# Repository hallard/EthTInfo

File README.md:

# Ethernet Teleinfo Shield for Olimex ESP32 POE

This shield is to be combined with [Olimex ESP32 POE board](https://www.olimex.com/Products/IoT/ESP32/ESP32-POE/open-source-hardware) to get French energy meter called Teleinfo (AKA TIC) 

It is mainly needed when your smartmeter his far from house and WiFi signal too weak and/or if you don't have power near your smartmeter to power Denky, WeMos Teleinfo or any other type of board. Having Ethernet near smart mater and you done with POE, Olimex board and this Shield.

It has the following features:

- Teleinfo Reader interface
- Blue LED to see if Teleinfo signal is received
- Trimmer to allow TIC sensitivity change without soldering resistors
- RGB User Led

It is a plug and play board, nothing to solder or assemble.

# History

**v1.1**

- Route RGB Led to GPIO5 instead of GPO2 (used by SD card)
- Change RGB Led to 2020 package

**v1.0**

- First fully working prototype

# Detailed Description

## Connectivity

The shield is connected thru Olimex UExt connector

Look at the schematics for more informations, easy to understand. Wiring is as follow:

| Pin Function | ESP32 | 
|  :---        | :---: | 
| Téléinfo Rx  | GPIO36 | 
| RGB Led      | GPIO5 (V1.1) | 
| RGB Led      | GPIO2 (V1.0) | 

Unfortunately RGB led share the same pin than SD Card GPIO2 so if you want to use RGB LED you need to disable SD Card GPIO mapping and vice versa

# Schematics

# Boards

# Firmware 

It's compatible with Arduino IDE, Visual Studio Code and also Micro Python.

You can write your own and use with [LibTeleinfo](https://github.com/hallard/LibTeleinfo) library I wrote if you want to get rid of driving teleinfo stuff (chekout some [examples](ttps://github.com/hallard/LibTeleinfo/tree/master/examples)).

## Tasmota

But I strongly suggest using amazing [Tasmota](https://tasmota.github.io/docs/) firmware, all is already done and well done.

Please check Teleinfo official tasmota [documentation](https://tasmota.github.io/docs/Teleinfo/) so see how to configure your device depending on smartmeter type and what options you need.

### Nicolas's builds

Nicolas @NicolasBernaerts has made awesome changes on Tasmota to be able to show graph of consumption, history and other great features such has:

- Ecowatt server to publish RTE Ecowatt signals
- TCP server to live stream teleinfo data
- FTP server to easily retrieve graph data

You can find more information on his dedicated [repo](https://github.com/NicolasBernaerts/tasmota/tree/master/teleinfo) and also ready made build.

### Tasmota Unofficial builds

Teleinfo is not member of official Tasmota builds. So you need to build your own with `USE_TELEINFO` define. 
But Tasmota team agreed it's not simple to build for end users, and they now provide unofficial build that follow developement branch, this mean you always have an up to date build with latest code available. Of course we added Teleinfo (ESP8266 and ESP32) builds in this unofficial build process so you have nothing to install and compile/link (building). You can't go easier.

And as a cherry on the cake, easy flasher tools (web version and executable one) will present Teleinfo firmware so you are able to flash teleinfo firmware in less than 1 minute. You can check detail [here](https://github.com/Jason2866/Tasmota-specials) but here how to do that.

- Launch [Web Flasher here](https://jason2866.github.io/Tasmota-specials/) 
- Select Teleinfo 
- Select Serial port, and click `install`

Once done something like that

After flashed, you should now see a new access point named `tasmota_aabbcc_xxxx` where you can connect to configure your WiFi for the device to connect on.

Alternatively, if you connect serial console and reset the device you should see Serial logs like that
```
[12:38:28]00:00:00.001 HDW: ESP32-D0WD-V3 v3.0 
[12:38:28]00:00:00.079 UFS: FlashFS mounted with 312 kB free
[12:38:28]00:00:00.080 TFS: File '.settings' not found
[12:38:28]00:00:00.082 TFS: File '.settings.lkg' not found
[12:38:28]00:00:00.082 CFG: Use defaults
[12:38:28]00:00:00.193 QPC: Reset
[12:38:29]00:00:00.415 BRY: Berry initialized, RAM used 4540 bytes
[12:38:29]00:00:00.427 Project tasmota - Tasmota Version 13.2.0.3(teleinfo)-2_0_14(2023-12-05T15:04:33)
[12:38:29]00:00:00.532 WIF: WifiManager active for 3 minutes
[12:38:29]00:00:01.064 HTP: Web server active on tasmota-88D0C4-4292 with IP address 192.168.4.1
```

If you want to deep into this process or just curious, you can check out it's [here](https://github.com/Jason2866/Tasmota-specials)

:memo: If you have some issues flashing with Web Flasher, do not hesitate to use another awesome tool [ESP Flasher](https://github.com/Jason2866/ESP_Flasher), with this one you can see exactly what's going on in case of issue because it has built in console. Usefull also after reboot of the device because console still active. This is the one I'm using day by day. In this case you need to download firmware to flash first [here](https://github.com/Jason2866/Tasmota-specials/tree/firmware/firmware/tasmota/other). Download firmware `tasmota-teleinfo`

You can take a look on `autoconf` [folder](https://github.com/tasmota/autoconf/tree/main/raw/esp32/EthTinfo_V1.0) to see some of init commands used on EthTinfo.

:memo: Don't forget to reset Energy counters on first boot with console command `EnergyTotal 0` if you have erratic values. 

### Autoconf 

Another awesome feature of Tasmota is the ability to download configuration profile, and guess what, we done it for EthTinfo, just go to configuration option, select Autoconfig and then choose in the list `EthTinfo` and here you are, ne need to copy/paste template, it's done by autoconfig.
If you want to deep into this process or just curious, you can check out it's [here](https://github.com/tasmota/autoconf)

### Tasmota template

I strongly suggest using awesome Tamsota autoconf feature but if you need Tasmota template for EThTinfo, here it it

<!--
#### V1.1 

With SD Card and RGB Led
```json
{"NAME":"EthTinfo (Olimex ESP32)","GPIO":[1,1,8864,1,0,1376,0,0,5536,1,8832,8800,0,0,5600,1,1,1,1,5568,1,1,1,1,0,0,0,0,1,1,32,1,5632,1,1,1],"FLAG":0,"BASE":1}
```
-->

#### V1.1 With SD Card And RGB Led

```json
{"NAME":"EthTinfo (Olimex ESP32)","GPIO":[1,1,8864,1,0,1376,0,0,5536,1,8832,8800,0,0,5600,1,1,1,1,5568,1,1,1,1,0,0,0,0,1,1,32,1,5632,1,1,1],"FLAG":0,"BASE":1}
```

#### V1.0 With SD Card (No RGB Led)

```json
{"NAME":"EthTinfo (Olimex ESP32)","GPIO":[1,1,8864,1,0,1,0,0,5536,1,8832,8800,0,0,5600,1,1,1,1,5568,1,1,1,1,0,0,0,0,1,1,32,1,5632,1,1,1],"FLAG":0,"BASE":1}
```

#### V1.0 With RGB Led (No SD Card)

```json
{"NAME":"EthTinfo (Olimex ESP32)","GPIO":[1,1,1376,1,0,1,0,0,5536,1,1,1,0,0,5600,1,1,1,1,5568,1,1,1,1,0,0,0,0,1,1,32,1,5632,1,1,1],"FLAG":0,"BASE":1}
```

## Berry Scripting 

Now you can personalize code with [Berry language](https://tasmota.github.io/docs/Berry/). Check out some Berry samples [here](https://github.com/arendst/Tasmota/blob/development/tasmota/berry/examples/)

You can do that by going to Berry console from Tasmota WEB user interface.

### Drive RGB LED depending on actual power

Here is a Berry example, goal is to follow real time consumption driving on board RGB Led depending on current Power consumption (low green then going to red when reaching maximum current of your contract)

```python
#-
# example of using Berry script to change the led color
# accordingly to power consumption
# using Denky, WeMos Teleifno or EthTinfo (French Teleinfo reader)
-#

#- define the global symbol for reference -#
runcolor = nil

def runcolor()
  var max_contrat = 30 # contrat 30A
  var i = energy.current
  #print(i)
  var red = tasmota.scale_uint(int(i), 0, max_contrat, 0, 255)
  var green = 255 - red
  var channels = [red, green, 0]
  light.set({"channels":channels, "bri":64, "power":true})
  tasmota.set_timer(2000, runcolor)
end

#- run animation -#
runcolor()
```

### Send data to Emoncms with Berry 

What's magic with Berry is the ability to do basic stuff with data, in this example we will intercept MQTT send message by Energy driver, do some calc and send data to Emoncms every 15 seconds and also to drive RGB Led from Green (low load) to Red (approach max subscription)

Modifiy API key with your, and copy paste the following code into Berry Console. Tst and validate if all is okay for you.

Once all is fine, you paste the code into a file named `autoexec.be` on the Tasmota Filesystem so it will be executed each time Tasmota device starting.

#### Mode Historique (contrat heures creuses)

```python
import json

var api_url = "https://emoncms.org/input/post"
var api_key = "YOUR_EMON_API_WRITE_KEY"
var node_name = "NODE_NAME"
var post_every = 15000 # post evert 15 seconds
var payload = {}

def send_emoncms()
  # Convert JSON object to string 
  var obj_json = json.dump(payload)

  # Create URL to call
  var param="?fulljson="+obj_json + "&node="+node_name + "&apikey="+api_key 
  # Post Data to EMONCMS
  var cl = webclient()
  cl.begin( api_url + param)
  var r =  cl.GET()
  tasmota.set_timer(post_every, send_emoncms)
end

def setcolor(iinst, isousc)
  var red = tasmota.scale_uint(iinst, 0, isousc, 0, 255)
  var green = 255 - red
  var channels = [red, green, 0]
  light.set({"channels":channels, "bri":64, "power":true})
end

# set global payload the field we need
def rule_tic(value, trigger)
  # Got Heures Creuses contract so I will calculate total consumption
  # adding Heures Creuses (HCHC) + Heures Pleines (HCHP) and create new value for emoncms 
  # Change label depending on name for your contract type
  var htot = value['HCHP'] + value['HCHC'] # mode historique
  # Create new value HTOT converted to kWH
  payload['HTOT'] = htot / 1000.0
  # Calculate current percent Load 
  var iinst = value['IINST']  # mode historique
  var isousc= value['ISOUSC'] # mode historique

  if iinst != nil && isousc != nil 
    # Drive RGB LED
    setcolor(iinst, isousc)
    if isousc > 0
      load = 100 * iinst / isousc
      payload['LOAD'] = load
    end
  end

  # Set values we need to send to emoncms
  payload['ADCO']  = value['ADCO']
  payload['HCHP']  = value['HCHP']
  payload['HCHC']  = value['HCHC']
  payload['ISOUSC']= isousc
  payload['PAPP']  = value['PAPP']
  payload['IINST'] = iinst

end

def start()
  # Callback on each frame interception
  tasmota.add_rule("TIC",rule_tic)
  # fire 1st post in 5s 
  tasmota.set_timer(5000, send_emoncms)
end

# delay start to have time to get full frame
tasmota.set_timer(10000, start)

```

#### Mode Standard (contrat heures creuses)

```python
import json

var api_url = "https://emoncms.org/input/post"
var api_key = "YOUR_EMON_API_WRITE_KEY"
var node_name = "NODE_NAME"
var post_every = 15000 # post evert 15 seconds
var payload = {}

def send_emoncms()
  # Convert JSON object to string 
  var obj_json = json.dump(payload)

  # Create URL to call
  var param="?fulljson="+obj_json + "&node="+node_name + "&apikey="+api_key 
  # Post Data to EMONCMS
  var cl = webclient()
  cl.begin( api_url + param)
  var r =  cl.GET()
  tasmota.set_timer(post_every, send_emoncms)
end

def setcolor(iinst, isousc)
  var red = tasmota.scale_uint(iinst, 0, isousc, 0, 255)
  var green = 255 - red
  var channels = [red, green, 0]
  light.set({"channels":channels, "bri":64, "power":true})
end

# set global payload the field we need
def rule_tic(value, trigger)
  # Got Heures Creuses contract so I will calculate total consumption
  # Calculate current percent Load 
  var iinst = value['IRMS1']  
  var isousc= value['PREF']*5 

  if iinst != nil && isousc != nil 
    # Drive RGB LED
    setcolor(iinst, isousc)
    if isousc > 0
      load = 100 * iinst / isousc
      payload['LOAD'] = load
    end
  end

  # Here I keep name of historique mode
  payload['ADCO']  = value['ADSC']
  payload['HTOT']  = value['EAST'] / 1000 # I need kWh
  payload['HCHP']  = value['EASF01']
  payload['HCHC']  = value['EASF02']
  payload['ISOUSC']= isousc
  payload['PAPP']  = value['SINSTS']
  payload['IINST'] = iinst

end

def start()
  # Callback on each frame interception
  tasmota.add_rule("TIC",rule_tic)
  # fire 1st post in 5s 
  tasmota.set_timer(5000, send_emoncms)
end

# delay start to have time to get full frame
tasmota.set_timer(10000, start)

```

### Custom WEB Interface

If you are not happy with values on the WEB interface you can totaly change them to fit your needs.

You can add new values to display or disable all values displayed and use you own or even some calculated ones.

To disable all current values displayed please use the following command in console (not the berry one)

```
backlog0 WebSensor0 0 ; WebSensor1 0 ; WebSensor2 0 ; WebSensor3 0
```

Then you can add Teleinfo driver (this one as example) into a file named `teleinfo.be`

This is just an example please fill it to your needs. This one display Total `EAST` index, `URMS1` and `IRMS1` on web interface

```python
# Teleinfo driver written in Berry
# Support for Teleinfo custom values from choosen fields returned by smart meter
 
class TELEINFO: Driver

  # Global var Needed
  var east
  var irms
  var urms

  def init()
    # initialize globals

    # Don't display original sensors on WebUI, we want just our ones
    tasmota.cmd("backlog0 WebSensor0 0 ; WebSensor1 0 ; WebSensor2 0 ; WebSensor3 0")

    # create rules to trigger when Teleinfo values updates 
    # Use Teleinfo Etiquette Names to get whatever value you need
    tasmota.add_rule("TIC#EAST", /value -> self.trigger_east(value))
    tasmota.add_rule("TIC#IRMS1", /value -> self.trigger_irms(value))
    tasmota.add_rule("TIC#URMS1", /value -> self.trigger_urms(value))
  end

  def trigger_east(index)
    self.east = index
  end

  def trigger_irms(i)
    self.irms = i
    # DEBUG print("irms:", i)
  end

  def trigger_urms(u)
    self.urms = u
    # DEBUG print("urms:", u)
  end

  # trigger a read every second 
  def every_second()
    # DEBUG print("sensors:",tasmota.read_sensors())
  end

  # display sensor value in the web UI
  def web_sensor()
    import string
    var msg = string.format(
            "{s}Consommation{m}%d Wh{e}"
            "{s}Tension RMS{m}%d V{e}"
            "{s}Intensité RMS{m}%d A{e}", 
             self.east, self.urms, self.irms )

    tasmota.web_send_decimal(msg)
  end

end

# Instantiate the driver
teleinfo = TELEINFO()
# add it to Tasmota
tasmota.add_driver(teleinfo)

```

Then you need to load and start it into your `autoexec.be` file. just add followin at the end of the file

```python
# Auto start teleinfo driver
load("teleinfo.be")
```

#### Here how it looks like

## Working board 

# Support and discussion

If you have any issue or just want to discuss on this project, please use community [forum](https://community.ch2i.eu/category/20)

# License

This work is licensed under a [Creative Commons Attribution-NonCommercial-ShareAlike 4.0 International License](https://creativecommons.org/licenses/by-nc-sa/4.0/)    
If you want to do commercial stuff with this project, please contact [CH2i company](https://ch2i.eu/en#support) so we can organize an simple agreement.

# Lazy building your own? 

You can order this module fully assembled with some extra on [tindie][1] or on [Lectronz](https://lectronz.com/products/ethtinfo).

European customers may prefer ordering on Lectronz, which offers additional payment methods and pricing in Euros.

# Misc

See news and other projects on my [blog][2] 
 
[1]: https://www.tindie.com/products/33668/
[2]: https://hallard.me

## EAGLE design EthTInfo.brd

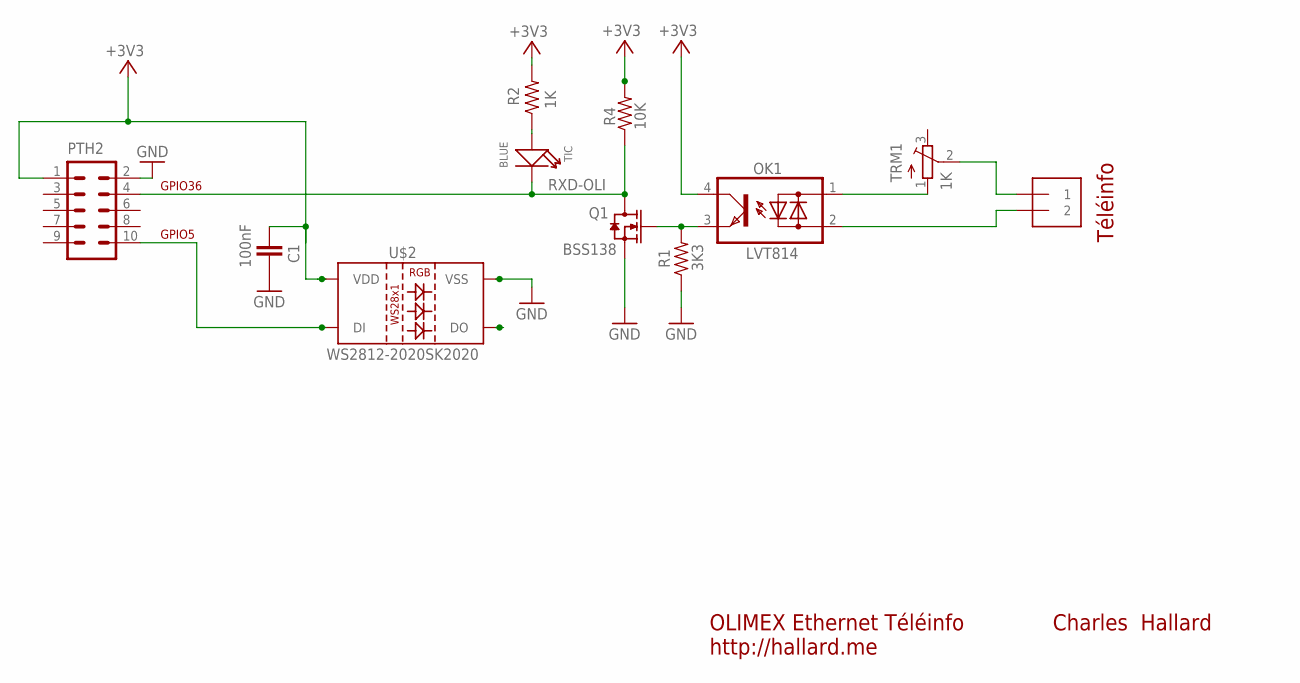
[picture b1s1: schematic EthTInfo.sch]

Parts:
C1: 100nF; 0402-CAP-OK
J1: 1X2-3.5MM-3.5MM; 1X2-3.5MM
OK1: LVT814; DIL4-SMD
PTH2: ML10FEMALE; ML10-FEMALE
Q1: BSS138; SOT-323-3
R1: 3K3; 0402-RES
R2: 1K; 0402-RES
R4: 10K; 0402-RES
TIC: BLUE; LED-0402
TRM1: 1K; TC33X
U$2: WS2812-2020SK2020; SK6805-2020

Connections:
3V3: C1.2, OK1.4 (C), PTH2.1, R2.2, R4.2, U$2.1 (VDD)
GND: C1.1, PTH2.2, Q1.2 (S), R1.1, U$2.3 (VSS)
unnamed: OK1.3 (E), Q1.1 (G), R1.2
unnamed: R2.1, TIC.+
unnamed: J1.1, TRM1.2 (S)
unnamed: J1.2, OK1.2 (AC2)
unnamed: PTH2.10, U$2.4 (DI)
unnamed: OK1.1 (AC1), TRM1.1 (A)
RXD-OLI: PTH2.4, Q1.3 (D), R4.1, TIC.-

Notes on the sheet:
OLIMEX Ethernet Téléinfo http://hallard.me
Charles Hallard
Téléinfo
GPIO5
GPIO36

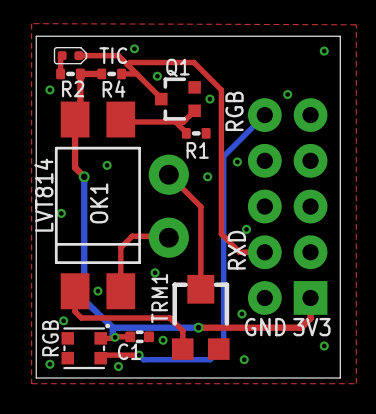
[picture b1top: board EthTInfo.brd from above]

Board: 2 copper layers, 16.9 x 19.0 mm, 11 parts (1 on the bottom side), 9 nets.

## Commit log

2024-02-10 fix template name
2024-02-10 added uext connector
2024-02-10 fixed links
2024-02-10 added why this shield
2024-02-10 added tindie link
2025-12-10 Bump to V1.1
    Bump to V1.1
2025-12-10 Updated to reflect V1.1 documentation
    Updated to reflect V1.1 documentation
2025-12-10 DOC : Added V1.1 Tasmota Template
    DOC : Added V1.1 Tasmota Template
2026-04-26 docs: add Lectronz badges next to Tindie
2026-04-29 Switch to CC BY-NC-SA 4.0 license, add LICENSE file
2026-04-29 license: use pure CC BY-NC-SA 4.0 text for GitHub auto-detection
2026-04-29 license: add copyright header above CC BY-NC-SA 4.0 text
